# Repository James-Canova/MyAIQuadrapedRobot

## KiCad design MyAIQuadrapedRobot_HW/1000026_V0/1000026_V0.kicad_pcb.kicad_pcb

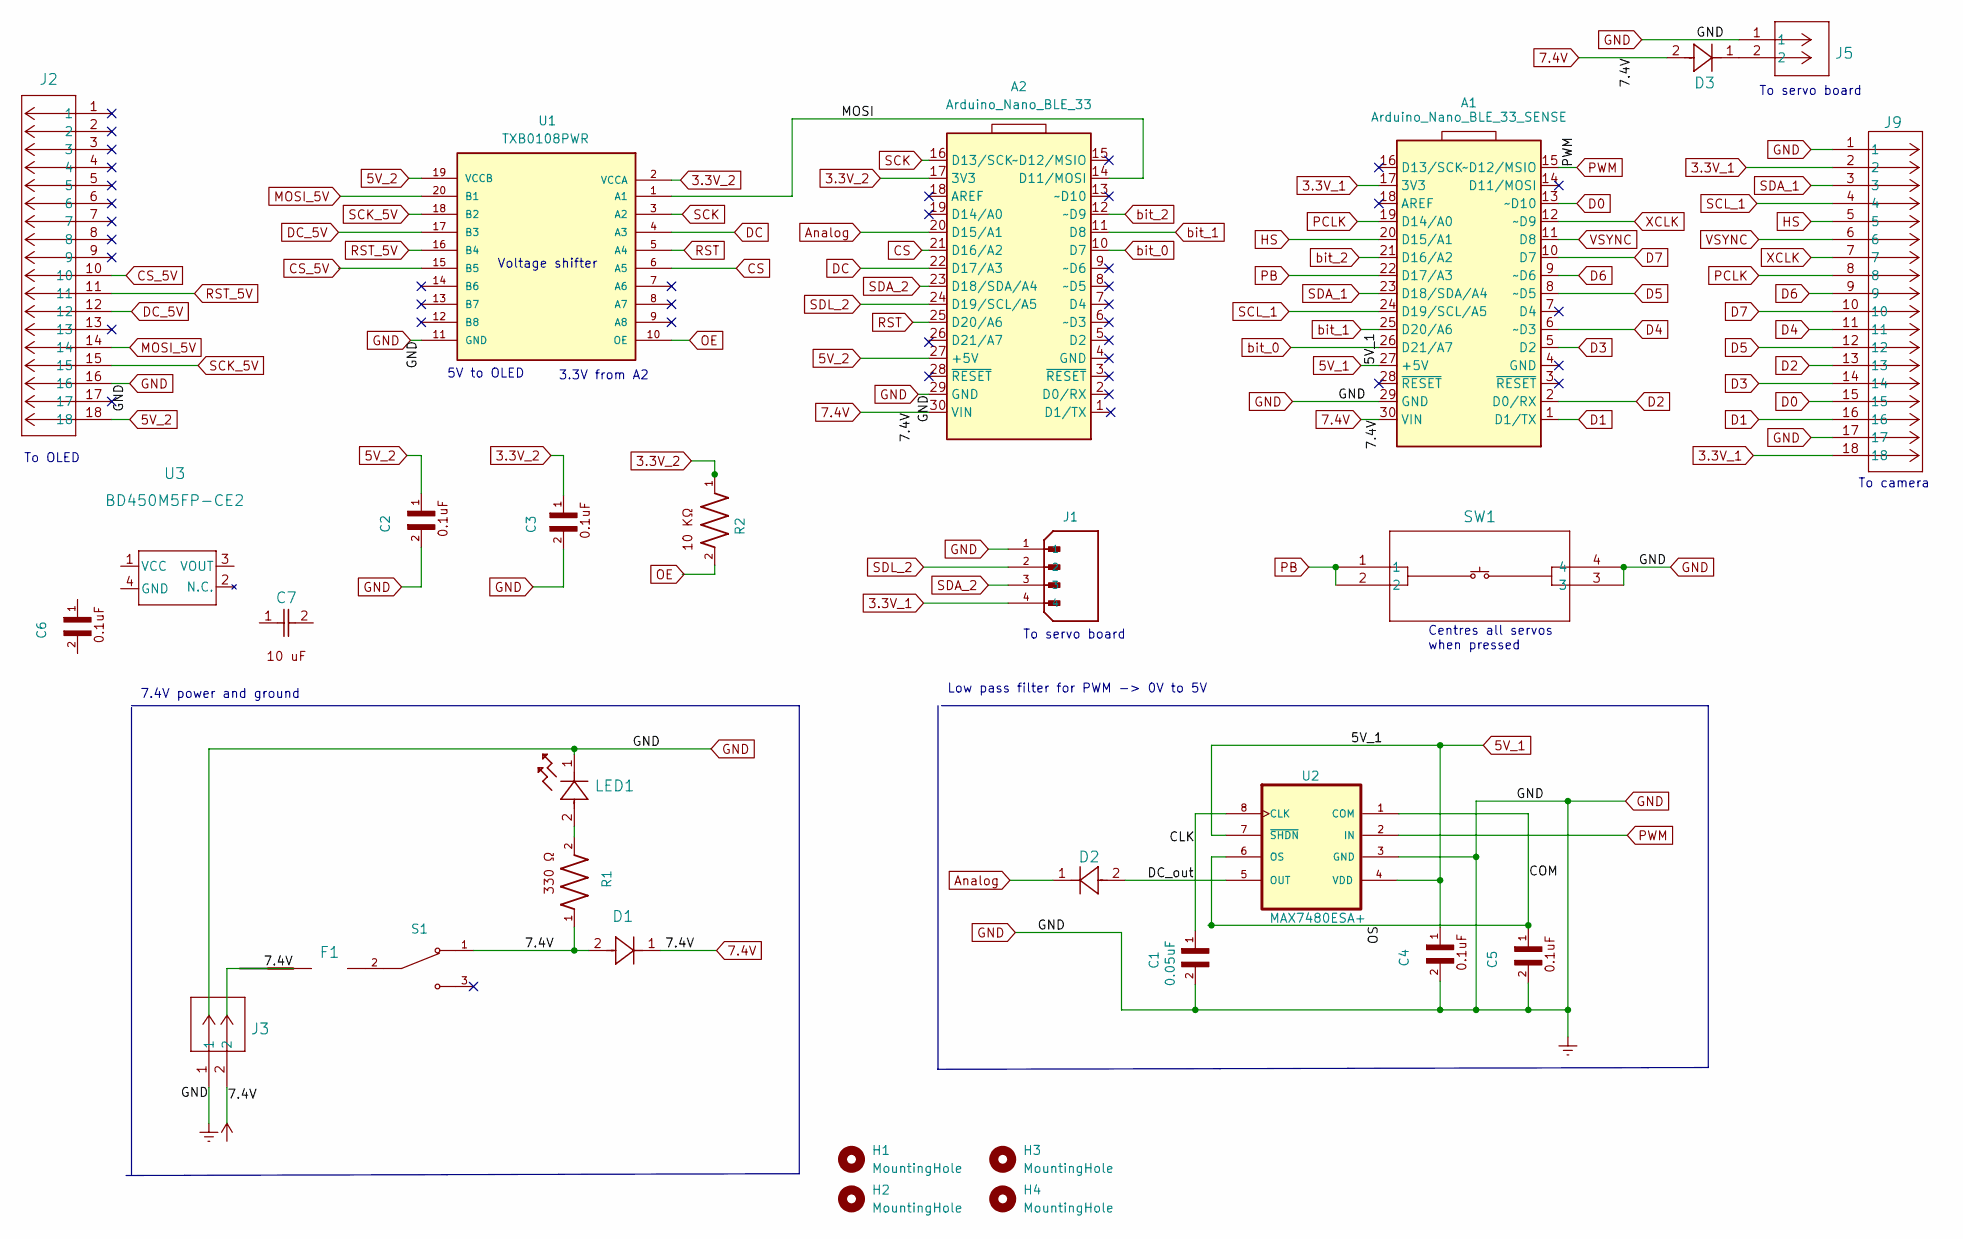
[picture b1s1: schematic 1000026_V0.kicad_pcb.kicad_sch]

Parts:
A1: Arduino_Nano_BLE_33_SENSE; Nano33BLE_with_headers
A2: Arduino_Nano_BLE_33; Nano33BLE_with_headers
C1: 12065C503JAT2A
C2, C3, C4, C5, C6: 12102C104KAT2A
C7: CL32A106KAULNNE
D1, D2, D3: 1N4148WX-TP; 1N4148WT
F1: RGEF300_Fuse; RGEF300HF
H1, H2, H3, H4: MountingHole; MountingHole_2.2mm_M2
J1: 533750410; PARTREV C
J2, J9: 0525591853; 525591853
J3, J5: 532580229; 0532580229
LED1: C503B-GAN-CB0F0791
R1: RMCF1210JT330R
R2: RMCF1210JT10K0
S1: 500SSP1S2M2QEA; PARTREV C
SW1: TL3305CF260QG
U1: TXB0108PWR; PARTREV H
U2: MAX7480ESA+; MAX7480ESA
U3: BD450M5FP-CE2

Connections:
3.3V_1: A1.17 (3V3), J1.4, J9.2, J9.18
3.3V_2: A2.17 (3V3), C3.1, R2.1, U1.2 (VCCA)
5V_1: A1.27 (+5V), C4.1, U2.4 (VDD), U2.7 (~SHDN)
5V_2: A2.27 (+5V), C2.1, J2.18, U1.19 (VCCB)
7.4V: A1.30 (VIN), A2.30 (VIN), D1.1, D1.2, D3.2, F1.1, J3.2, R1.1, S1.1
/CLK: C1.1, U2.8 (CLK)
/COM: C5.1, U2.1 (COM), U2.6 (OS)
/DC_out: D2.2, U2.5 (OUT)
/MOSI: A2.14 (D11/MOSI), U1.1 (A1)
Analog: A2.20 (D15/A1), D2.1
CS: A2.21 (D16/A2), U1.6 (A5)
CS_5V: J2.10, U1.15 (B5)
D0: A1.13 (~D10), J9.15
D1: A1.1 (D1/TX), J9.16
D2: A1.2 (D0/RX), J9.13
D3: A1.5 (D2), J9.14
D4: A1.6 (~D3), J9.11
D5: A1.8 (~D5), J9.12
D6: A1.9 (~D6), J9.9
D7: A1.10 (D7), J9.10
DC: A2.22 (D17/A3), U1.4 (A3)
DC_5V: J2.12, U1.17 (B3)
GND: A1.29 (GND), A2.29 (GND), C1.2, C2.2, C3.2, C4.2, C5.2, J1.1, J2.16, J3.1, J5.1, J9.1, J9.17, LED1.1, SW1.3, SW1.4, U1.11 (GND), U2.3 (GND)
HS: A1.20 (D15/A1), J9.5
MOSI_5V: J2.14, U1.20 (B1)
unnamed: D3.1, J5.2
unnamed: F1.2, S1.2
unnamed: LED1.2, R1.2
OE: R2.2, U1.10 (OE)
PB: A1.22 (D17/A3), SW1.1, SW1.2
PCLK: A1.19 (D14/A0), J9.8
PWM: A1.15 (~D12/MSIO), U2.2 (IN)
RST: A2.25 (D20/A6), U1.5 (A4)
RST_5V: J2.11, U1.16 (B4)
SCK: A2.16 (D13/SCK), U1.3 (A2)
SCK_5V: J2.15, U1.18 (B2)
SCL_1: A1.24 (D19/SCL/A5), J9.4
SDA_1: A1.23 (D18/SDA/A4), J9.3
SDA_2: A2.23 (D18/SDA/A4), J1.3
SDL_2: A2.24 (D19/SCL/A5), J1.2
VSYNC: A1.11 (D8), J9.6
XCLK: A1.12 (~D9), J9.7
bit_0: A1.26 (D21/A7), A2.10 (D7)
bit_1: A1.25 (D20/A6), A2.11 (D8)
bit_2: A1.21 (D16/A2), A2.12 (~D9)

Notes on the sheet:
3.3V from A2
To servo board
5V to OLED
Voltage shifter
To OLED
Low pass filter for PWM -> 0V to 5V
7.4V power and ground
To camera
Centres all servos when pressed

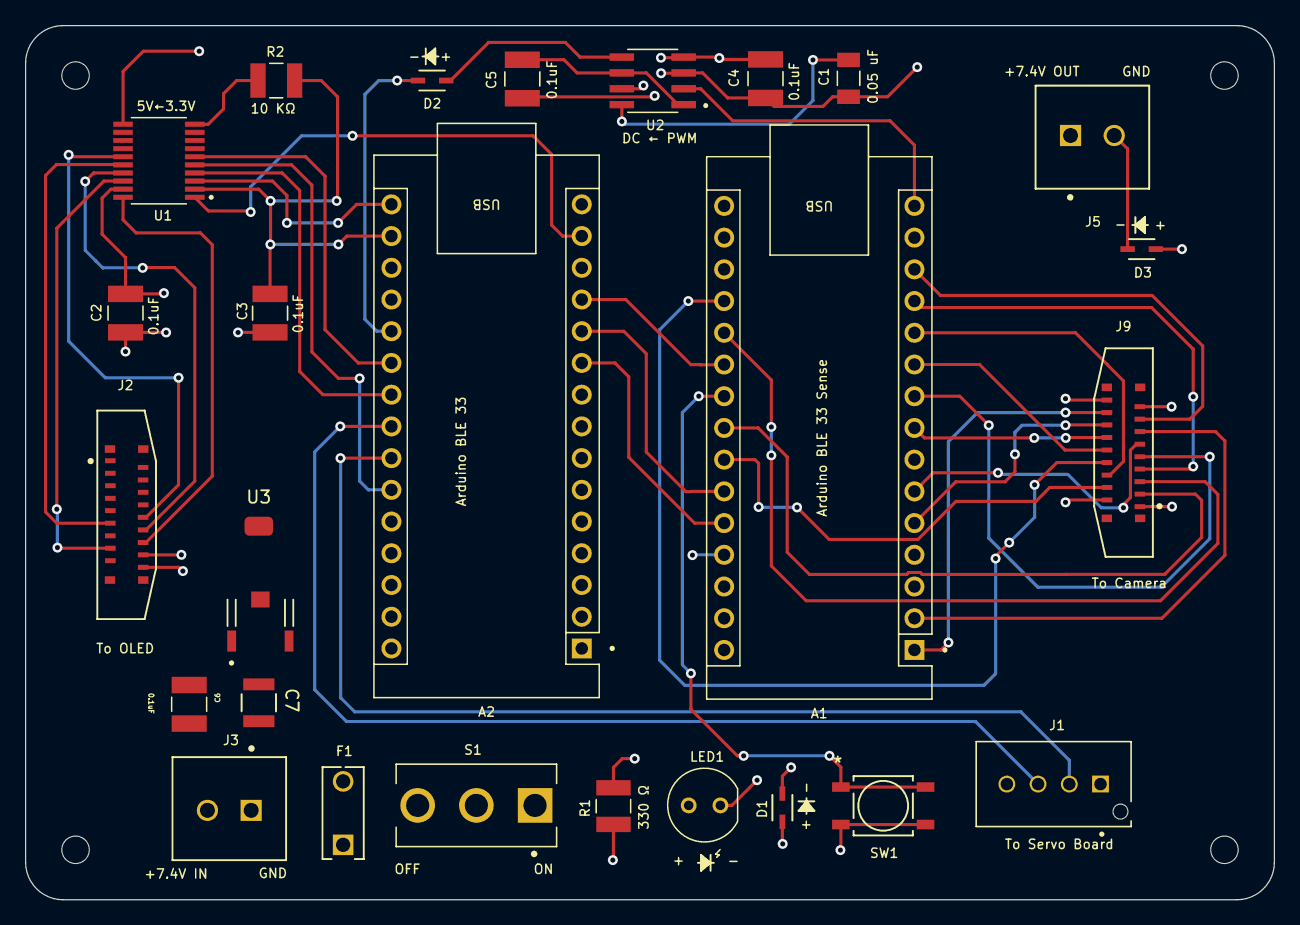
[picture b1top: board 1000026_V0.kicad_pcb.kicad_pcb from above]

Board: 4 copper layers, 100.0 x 70.0 mm, 30 parts (0 on the bottom side), 45 nets.

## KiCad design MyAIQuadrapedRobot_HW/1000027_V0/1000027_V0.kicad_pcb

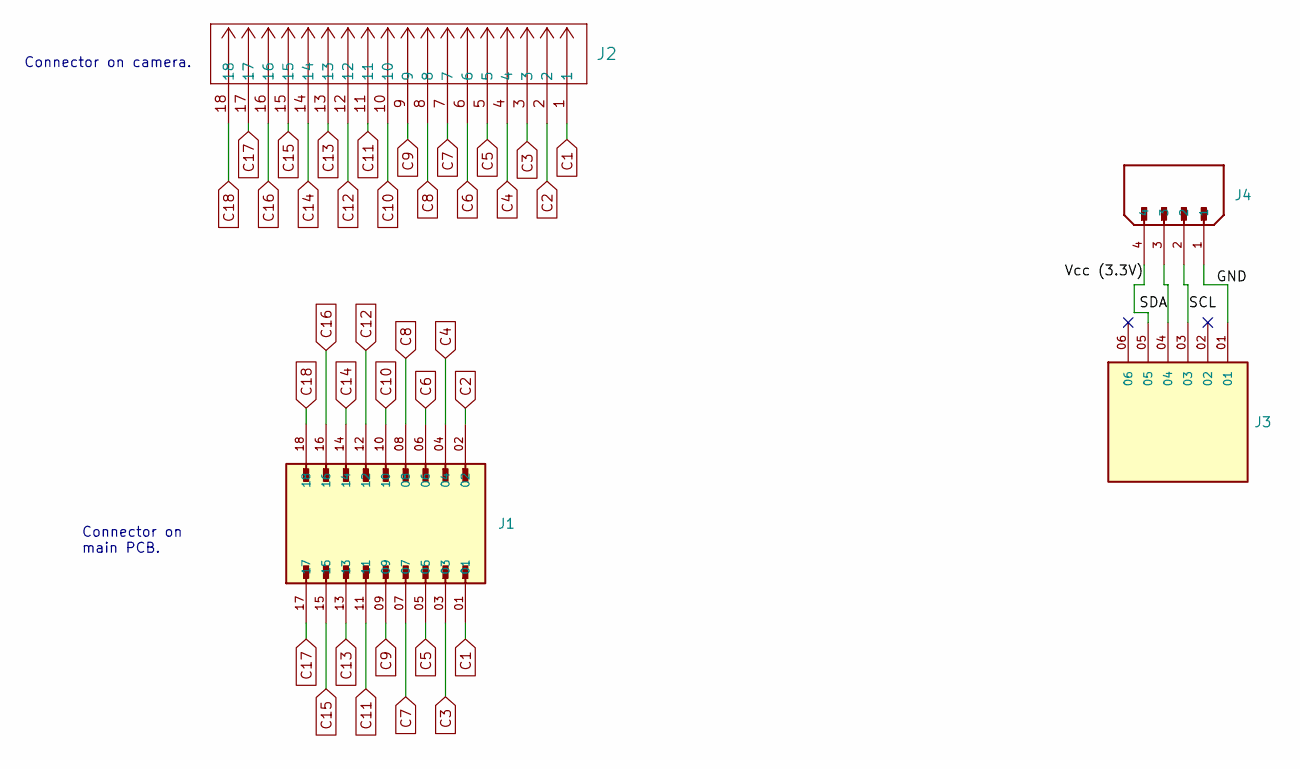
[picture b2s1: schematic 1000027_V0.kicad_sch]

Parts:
J1: 10076801-406T18LF_9_by_2_header; AMPHENOL_10076801-406T18LF; PARTREV E
J2: 0525591853; 525591853
J3: MTSW-106-12-L-S-790_6_by_1_header; SAMTEC_MTSW-106-12-L-S-790; PARTREV R
J4: 533750410; PARTREV C

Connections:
/GND: J3.01, J4.1
/SCL: J3.03, J4.2
/SDA: J3.04, J4.3
/Vcc (3.3V): J3.05, J4.4
C1: J1.01, J2.1
C2: J1.02, J2.2
C3: J1.03, J2.3
C4: J1.04, J2.4
C5: J1.05, J2.5
C6: J1.06, J2.6
C7: J1.07, J2.7
C8: J1.08, J2.8
C9: J1.09, J2.9
C10: J1.10, J2.10
C11: J1.11, J2.11
C12: J1.12, J2.12
C13: J1.13, J2.13
C14: J1.14, J2.14
C15: J1.15, J2.15
C16: J1.16, J2.16
C17: J1.17, J2.17
C18: J1.18, J2.18

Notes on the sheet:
Connector on main PCB.
Connector on camera.

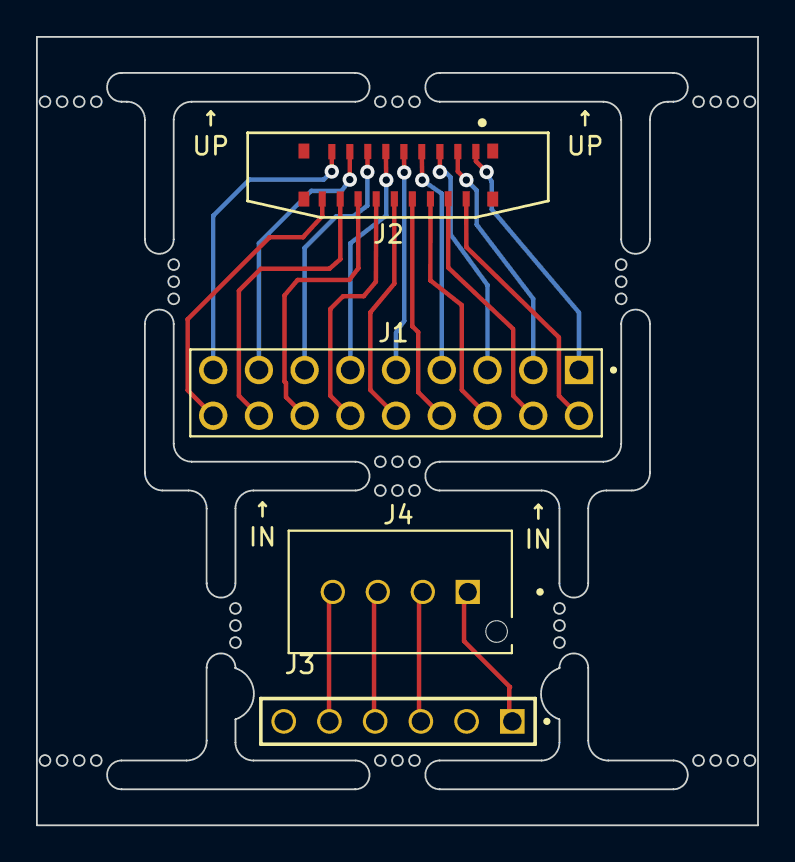
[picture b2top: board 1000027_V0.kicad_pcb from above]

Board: 2 copper layers, 40.1 x 43.8 mm, 4 parts (0 on the bottom side), 22 nets.

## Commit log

2023-06-04 First commit.
2023-06-04 Second commit.
2023-06-05 Development changes.
2023-06-05 Update of KiCad library in progress.
2023-06-06 KiCad library update complete.
2023-06-06 1000027_V0(a) ready for checking.
2023-06-07 All tracks in place but needs improvement.
2023-06-08 Clean up of tracks in progress.
2023-06-08 Checked, version V0a
2023-06-08 PCBs, V0a with Gerber files.
2023-06-28 Start of version V0b.
2023-07-01 Added some larger SMD library files
2023-07-02 Revisions in progress for change in sizes of some SMD components.
2023-07-02 Minor revisions.
2023-07-02 Moved LED to clear post.
2023-07-11 Added components for 5V regulator.

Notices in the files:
MyAIQuadrapedRobot_HW/1000026_V0/1000026_V0.kicad_pcb.kicad_pcb:
Copyright © James Canova,
August 2023,
parts and their libraries:
Copyright 2016 Accelerated Designs. All rights reserved.
